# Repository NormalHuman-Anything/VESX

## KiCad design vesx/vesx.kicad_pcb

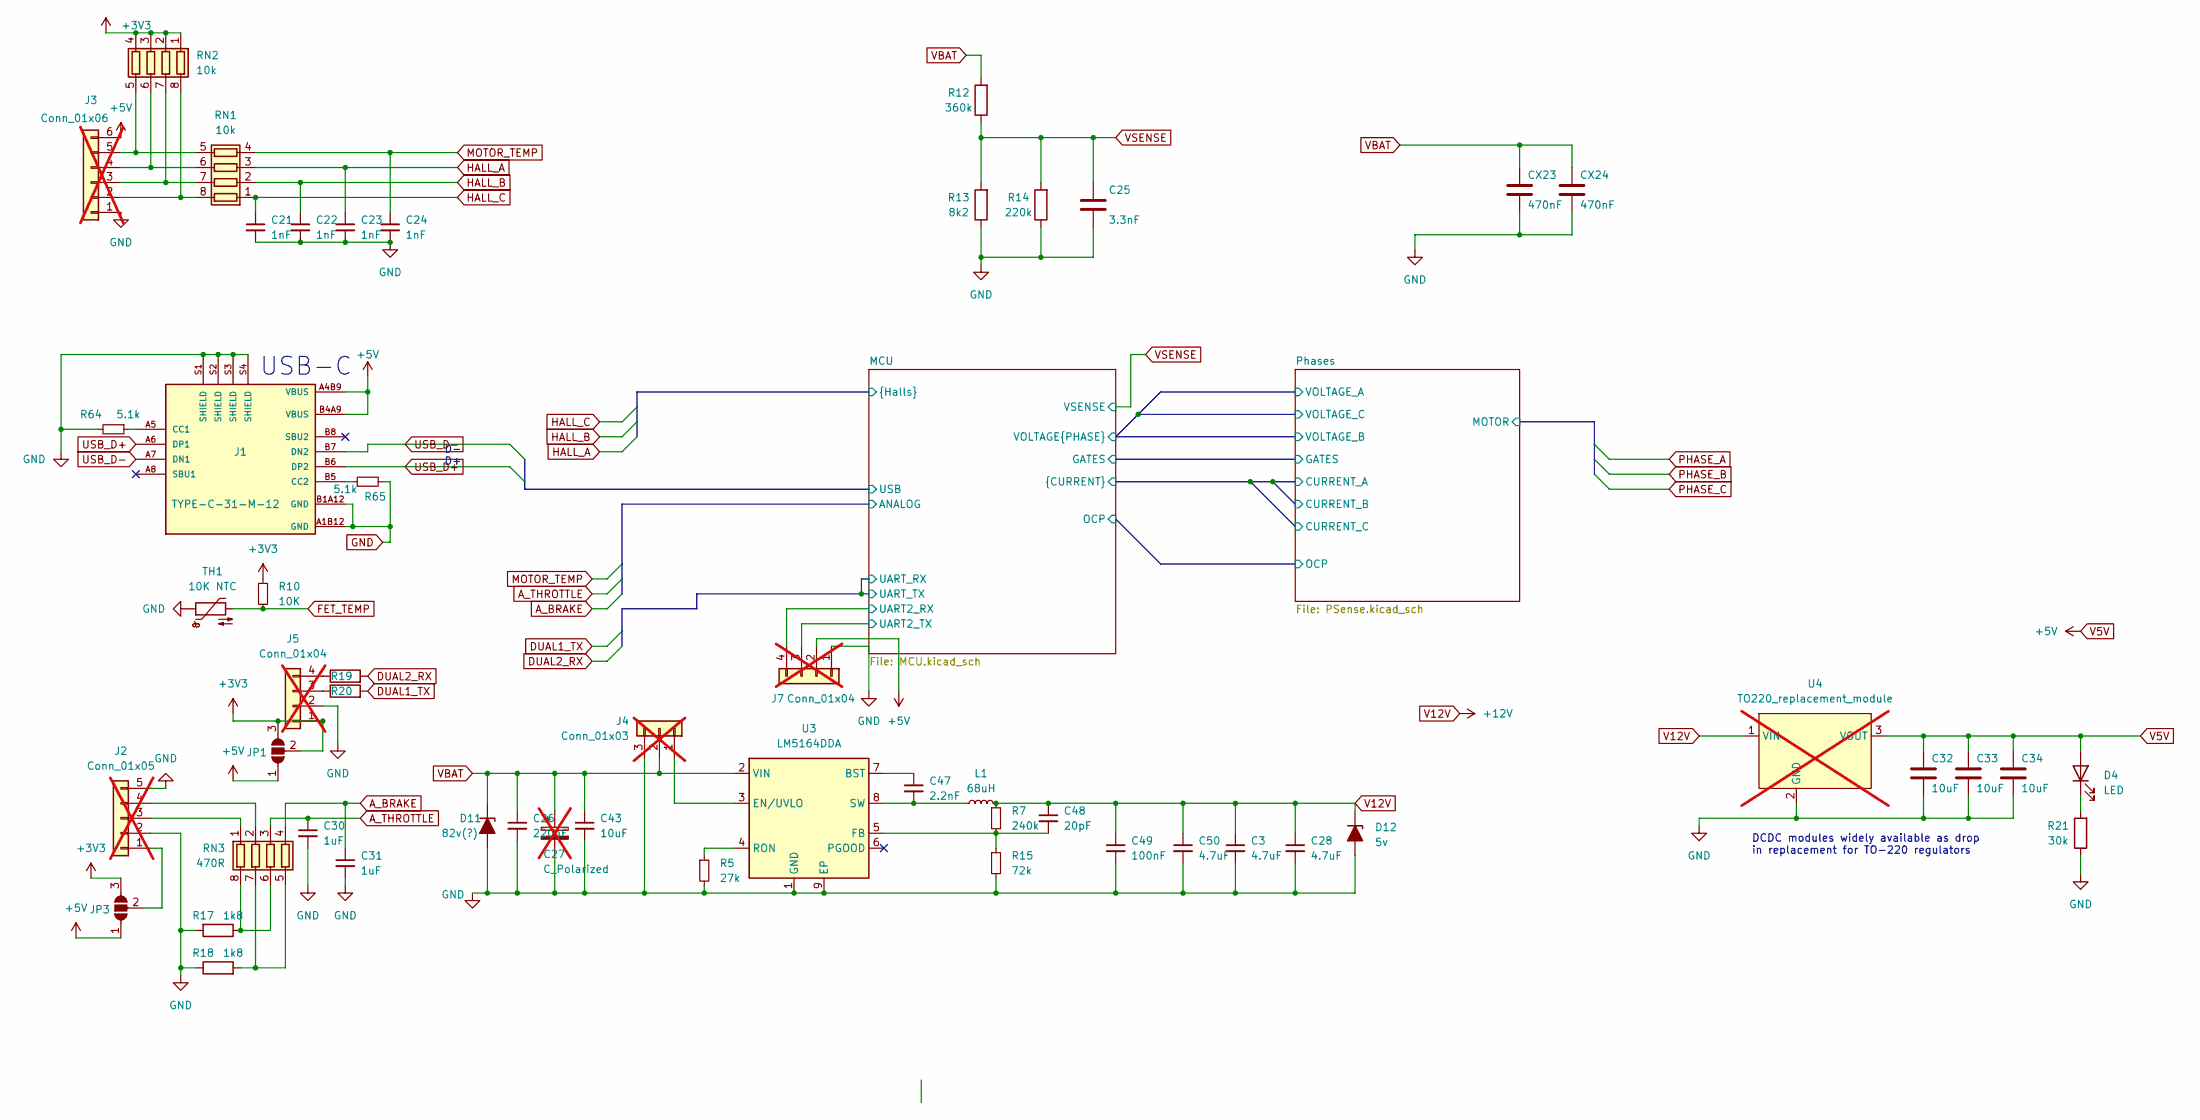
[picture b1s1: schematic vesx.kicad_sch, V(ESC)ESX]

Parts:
C3, C28, C50: 4.7uF; C_0603_1608Metric; LCSC C237615
C21, C22, C23, C24: 1nF; C_0603_1608Metric; LCSC C1588
C25: 3.3nF; C_0603_1608Metric; LCSC C1613
C26: 220nF; C_0603_1608Metric; LCSC C6119850
C27: C_Polarized; CP_Radial_D8.0mm_P3.50mm; not fitted
C30, C31: 1uF; C_0603_1608Metric; LCSC C15849
C32, C33, C34, C43: 10uF; C_0603_1608Metric; LCSC C96446
C47: 2.2nF; C_0603_1608Metric; LCSC C113804
C48: 20pF; C_0402_1005Metric; LCSC C343868
C49: 100nF; C_0603_1608Metric; LCSC C14663
CX23, CX24: 470nF; C_1210_3225Metric; LCSC C192761
D4: LED; LED_0603_1608Metric; LCSC C72041
D11: 82v(?); D_SOD-123F; LCSC C2903858
D12: 5v; D_SOD-323; LCSC C508230
J1: TYPE-C-31-M-12; USB_C_Receptacle_HRO_TYPE-C-31-M-12; PARTREV A; LCSC C165948
J2: Conn_01x05; JST_PH_B5B-PH-K_1x05_P2.00mm_Vertical; not fitted
J3: Conn_01x06; JST_PH_B6B-PH-K_1x06_P2.00mm_Vertical; not fitted
J4: Conn_01x03; JST_PH_B3B-PH-K_1x03_P2.00mm_Vertical; not fitted
J5: Conn_01x04; JST_PH_B4B-PH-K_1x04_P2.00mm_Vertical; not fitted
J7: Conn_01x04; PinHeader_1x04_P1.00mm_Vertical; not fitted
JP1, JP3: SolderJumper_3_Open; SolderJumper-3_P1.3mm_Open_RoundedPad1.0x1.5mm_NumberLabels
L1: 68uH; L_TracoPower_TCK-047_5.2x5.8mm; LCSC C5362907
R5: 27k; R_0603_1608Metric; LCSC C3016359
R7: 240k; R_0603_1608Metric; LCSC C269687
R10: 10K; R_0603_1608Metric; LCSC C25804
R12: 360k; R_0805_2012Metric; LCSC C17645
R13: 8k2; R_0603_1608Metric; LCSC C25981
R14: 220k; R_0603_1608Metric; LCSC C22961
R15: 72k; R_0603_1608Metric; LCSC C2828635
R17, R18: 1k8; R_0603_1608Metric; LCSC C4177
R19, R20: R100; R_0603_1608Metric; LCSC C22775
R21: 30k; R_0603_1608Metric; LCSC C22984
R64, R65: 5.1k; R_0402_1005Metric; LCSC C105872
RN1, RN2: 10k; R_Array_Concave_4x0603; LCSC C20624287
RN3: 470R; R_Array_Concave_4x0603; LCSC C25510
TH1: 10K NTC; R_0603_1608Metric; LCSC C167506
U3: LM5164DDA; HSOP-8-1EP_3.9x4.9mm_P1.27mm_EP2.41x3.1mm_ThermalVias; LCSC C477928
U4: TO220_replacement_module; not fitted

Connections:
+3V3: J5.1, JP1.2 (C), JP1.3 (B), JP3.3 (B), R10.1, RN2.1 (R1.1), RN2.2 (R2.1), RN2.3 (R3.1), RN2.4 (R4.1); also elsewhere on the board
/MCU/UART2_RX: J7.4; also elsewhere on the board
/MCU/UART2_TX: J7.3; also elsewhere on the board
A_BRAKE: C31.1, RN3.4 (R4.1); also elsewhere on the board
A_THROTTLE: C30.1, RN3.3 (R3.1); also elsewhere on the board
DUAL1_TX: R20.2; also elsewhere on the board
DUAL2_RX: R19.2; also elsewhere on the board
FET_TEMP: R10.2, TH1.2; also elsewhere on the board
GND: C3.2, C21.2, C22.2, C23.2, C24.2, C25.2, C26.2, C27.2, C28.2, C30.2, C31.2, C32.2, C33.2, C34.2, C43.2, C49.2, C50.2, CX23.2, CX24.2, D11.2 (A), D12.2 (A), J1.A1B12 (GND), J1.B1A12 (GND), J1.S1 (SHIELD), J1.S2 (SHIELD), J1.S3 (SHIELD), J1.S4 (SHIELD), J2.2, J2.5, J3.1, J4.3, J5.2, J7.1, R5.2, R13.1, R14.1, R15.2, R17.2, R18.1, R21.1, R64.2, R65.2, TH1.1, U3.1 (GND), U3.9 (EP), U4.2 (GND); also elsewhere on the board
HALL_A: C23.1, RN1.3 (R3.1)
HALL_B: C22.1, RN1.2 (R2.1)
HALL_C: C21.1, RN1.1 (R1.1)
MOTOR_TEMP: C24.1, RN1.4 (R4.1); also elsewhere on the board
unnamed: D4.1 (K), R21.2
unnamed: J1.A5 (CC1), R64.1
unnamed: J1.B5 (CC2), R65.1
unnamed: J2.1, JP3.2 (C)
unnamed: J2.3, RN3.1 (R1.1)
unnamed: J2.4, RN3.2 (R2.1)
unnamed: J3.2, RN1.8 (R1.2), RN2.8 (R1.2)
unnamed: J3.3, RN1.7 (R2.2), RN2.7 (R2.2)
unnamed: J3.4, RN1.6 (R3.2), RN2.6 (R3.2)
unnamed: J3.5, RN1.5 (R4.2), RN2.5 (R4.2)
unnamed: J4.1, U3.3 (EN/UVLO)
unnamed: J5.3, R20.1
unnamed: J5.4, R19.1
unnamed: R17.1, RN3.6 (R3.2), RN3.8 (R1.2)
unnamed: R18.2, RN3.5 (R4.2), RN3.7 (R2.2)
unnamed: C47.1, U3.7 (BST)
unnamed: C48.2, R7.2, R15.1, U3.5 (FB)
unnamed: R5.1, U3.4 (RON)
unnamed: C47.2, L1.1, U3.8 (SW)
USB_D+: J1.A6 (DP1), J1.B6 (DP2); also elsewhere on the board
USB_D-: J1.A7 (DN1), J1.B7 (DN2); also elsewhere on the board
V5V: C32.1, C33.1, C34.1, D4.2 (A), J1.A4B9 (VBUS), J1.B4A9 (VBUS), J3.6, J7.2, JP1.1 (A), JP3.1 (A), U4.3 (VOUT); also elsewhere on the board
V12V: C3.1, C28.1, C48.1, C49.1, C50.1, D12.1 (K), L1.2, R7.1, U4.1 (VIN); also elsewhere on the board
VBAT: C26.1, C27.1, C43.1, CX23.1, CX24.1, D11.1 (K), J4.2, R12.2, U3.2 (VIN); also elsewhere on the board
VSENSE: C25.1, R12.1, R13.2, R14.2; also elsewhere on the board

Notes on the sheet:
DCDC modules widely available as drop in replacement for TO-220 regulators
D- D+
USB-C

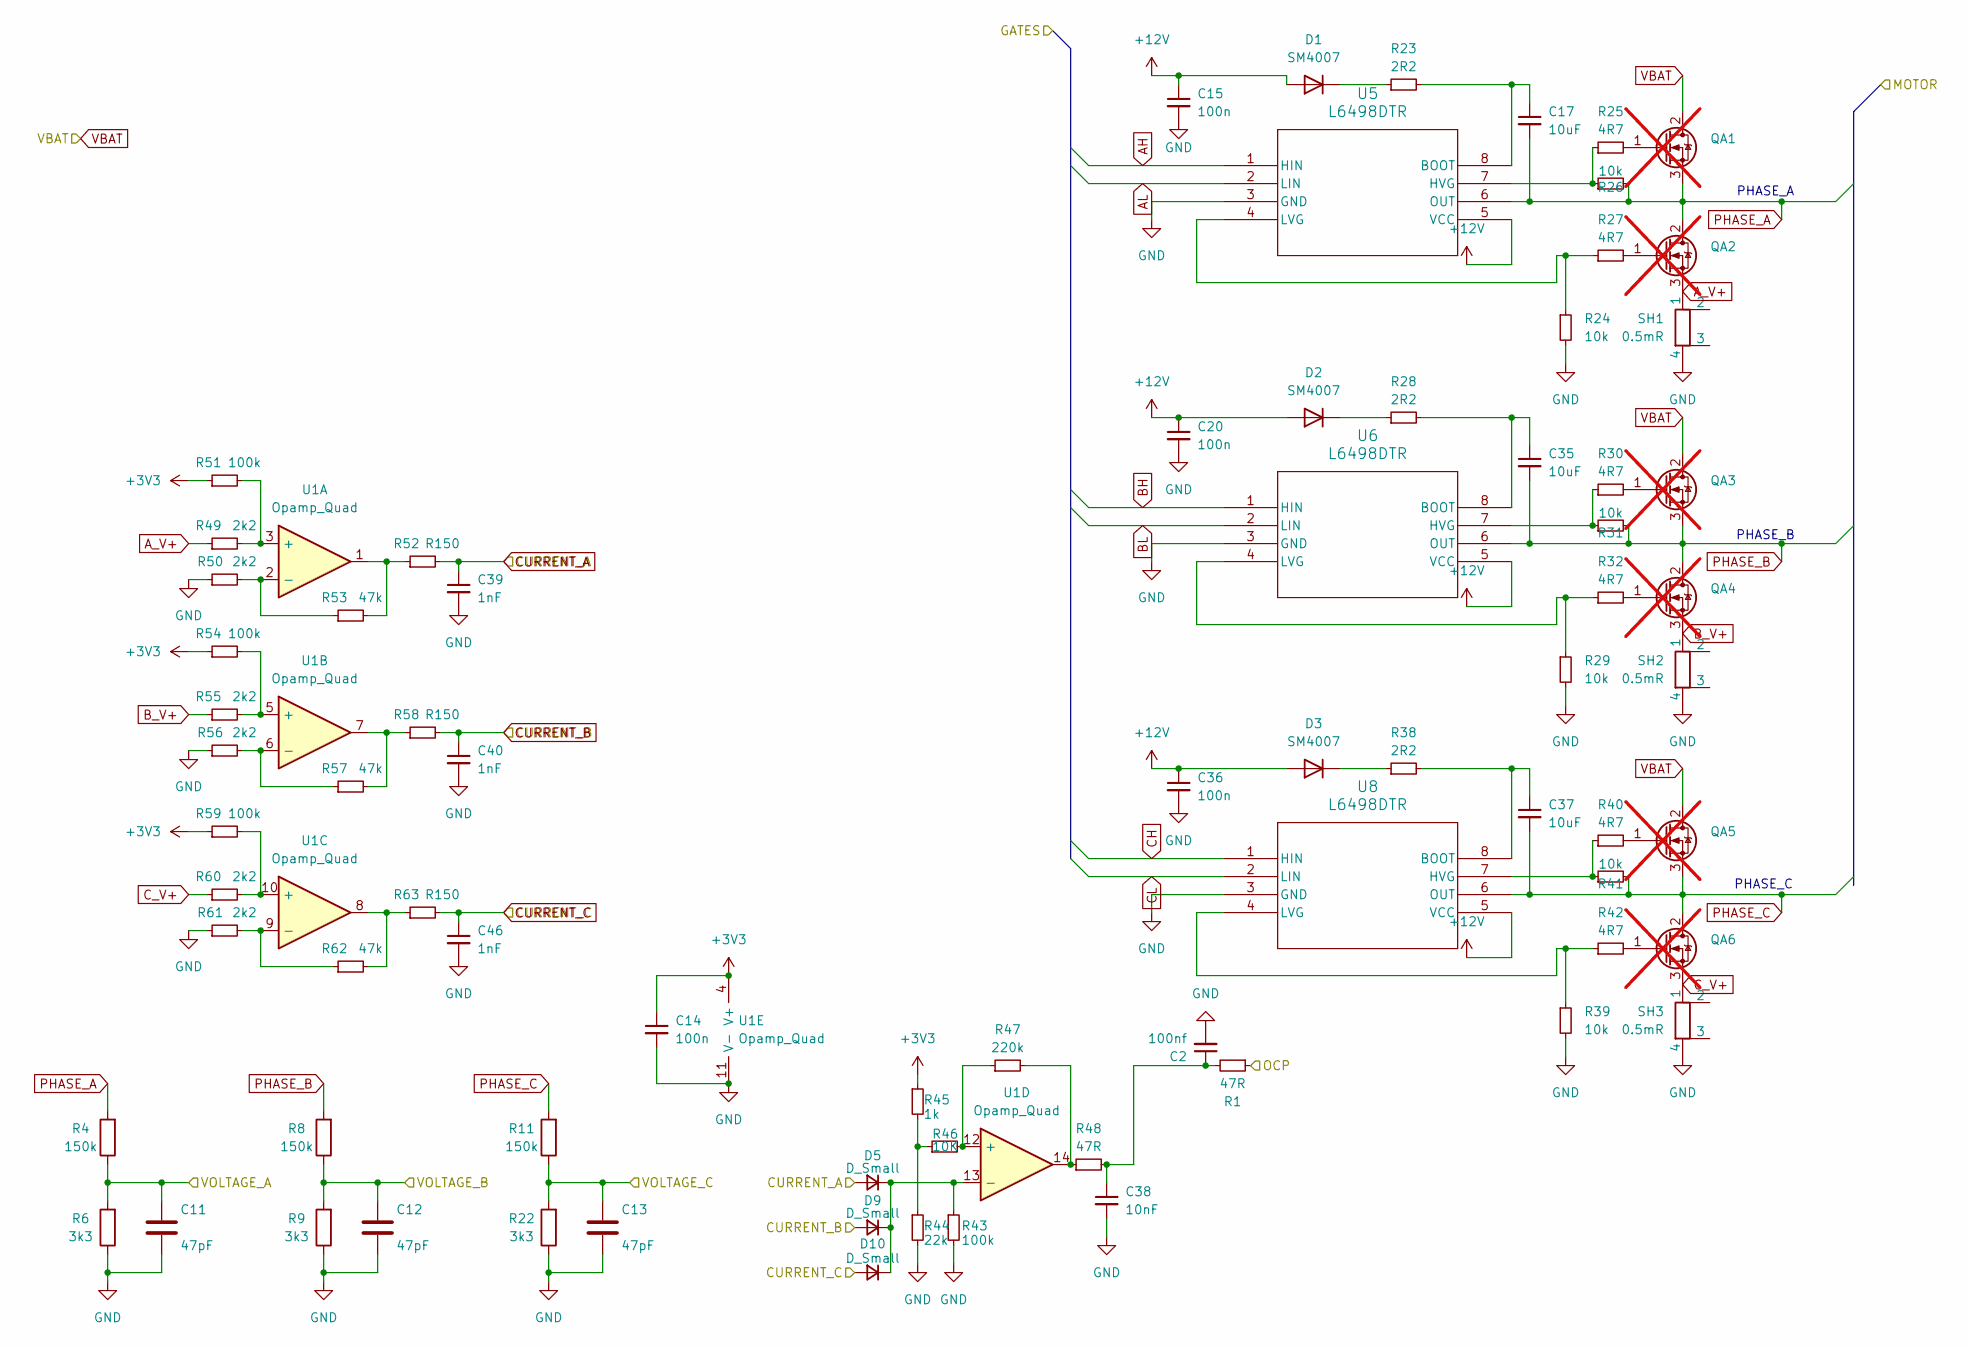
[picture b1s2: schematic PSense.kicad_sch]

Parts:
C2: 100nf; C_0402_1005Metric; LCSC C1525
C11, C12, C13: 47pF; C_0603_1608Metric; LCSC C1671
C14, C15, C20, C36: 100n; C_0603_1608Metric; LCSC C14663
C17, C35, C37: 10uF; C_0603_1608Metric; LCSC C96446
C38: 10nF; C_0603_1608Metric; LCSC C57112
C39, C40, C46: 1nF; C_0603_1608Metric; LCSC C1588
D1, D2, D3: SM4007; D_MELF; LCSC C412437
D5, D9, D10: D_Small; D_SOD-323; LCSC C191023
QA1, QA2, QA3, QA4, QA5, QA6: CRST030N10N; TO-220-3_Vertical; not fitted
R1: 47R; R_0402_1005Metric; LCSC C25118
R4, R8, R11: 150k; R_0805_2012Metric; LCSC C17470
R6, R9, R22: 3k3; R_0603_1608Metric; LCSC C22978
R23, R28, R38: 2R2; R_0603_1608Metric; LCSC C22939
R24, R26, R29, R31, R39, R41: 10k; R_0603_1608Metric; LCSC C25804
R25, R27, R30, R32, R40, R42: 4R7; R_0603_1608Metric; LCSC C23214
R43, R51, R54, R59: 100k; R_0603_1608Metric; LCSC C25803
R44: 22k; R_0603_1608Metric; LCSC C31850
R45: 1k; R_0603_1608Metric; LCSC C21190
R46: 10K; R_0603_1608Metric; LCSC C25804
R47: 220k; R_0603_1608Metric; LCSC C22961
R48: 47R; R_0603_1608Metric; LCSC C23182
R49, R50, R55, R56, R60, R61: 2k2; R_0603_1608Metric; LCSC C4190
R52, R58, R63: R150; R_0603_1608Metric; LCSC C22808
R53, R57, R62: 47k; R_0603_1608Metric; LCSC C25819
SH1, SH2, SH3: 0.5mR; Shunt_2512_6332Metric; LCSC C7178835
U1: Opamp_Quad; SOIC-14_3.9x8.7mm_P1.27mm; LCSC C695777
U5, U6, U8: L6498DTR; SO-8_STM; LCSC C500658

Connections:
+3V3: C14.1, R45.1, R51.1, R54.1, R59.1, U1.4 (V+); also elsewhere on the board
/MCU/OCP: R1.1; also elsewhere on the board
AH: U5.1 (HIN); also elsewhere on the board
AL: U5.2 (LIN); also elsewhere on the board
A_V+: QA2.3, R49.1, SH1.1
BH: U6.1 (HIN); also elsewhere on the board
BL: U6.2 (LIN); also elsewhere on the board
B_V+: QA4.3, R55.1, SH2.1
CH: U8.1 (HIN); also elsewhere on the board
CL: U8.2 (LIN); also elsewhere on the board
CURRENT_A: C39.1, D5.2 (A), R52.2; also elsewhere on the board
CURRENT_B: C40.1, D9.2 (A), R58.2; also elsewhere on the board
CURRENT_C: C46.1, D10.2 (A), R63.2; also elsewhere on the board
C_V+: QA6.3, R60.1, SH3.1
GND: C2.2, C11.2, C12.2, C13.2, C14.2, C15.2, C20.2, C36.2, C38.2, C39.2, C40.2, C46.2, R6.1, R9.1, R22.1, R24.2, R29.2, R39.2, R43.2, R44.2, R50.1, R56.1, R61.1, SH1.4, SH2.4, SH3.4, U1.11 (V-), U5.3 (GND), U6.3 (GND), U8.3 (GND); also elsewhere on the board
unnamed: C2.1, C38.1, R1.2, R48.2
unnamed: D1.1 (K), R23.1
unnamed: D2.1 (K), R28.1
unnamed: D3.1 (K), R38.1
unnamed: D5.1 (K), D9.1 (K), D10.1 (K), R43.1, U1.13 (-)
unnamed: QA1.1, R25.2
unnamed: QA2.1, R27.2
unnamed: QA3.1, R30.2
unnamed: QA4.1, R32.2
unnamed: QA5.1, R40.2
unnamed: QA6.1, R42.2
unnamed: R44.1, R45.2, R46.1
unnamed: R47.2, R48.1, U1.14
unnamed: R52.1, R53.2, U1.1
unnamed: R57.2, R58.1, U1.7
unnamed: R62.2, R63.1, U1.8
unnamed: R49.2, R51.2, U1.3 (+)
unnamed: R50.2, R53.1, U1.2 (-)
unnamed: R54.2, R55.2, U1.5 (+)
unnamed: R56.2, R57.1, U1.6 (-)
unnamed: R59.2, R60.2, U1.10 (+)
unnamed: R61.2, R62.1, U1.9 (-)
unnamed: R46.2, R47.1, U1.12 (+)
unnamed: C17.1, R23.2, U5.8 (BOOT)
unnamed: R25.1, R26.1, U5.7 (HVG)
unnamed: R24.1, R27.1, U5.4 (LVG)
unnamed: C35.1, R28.2, U6.8 (BOOT)
unnamed: R30.1, R31.1, U6.7 (HVG)
unnamed: R29.1, R32.1, U6.4 (LVG)
unnamed: C37.1, R38.2, U8.8 (BOOT)
unnamed: R40.1, R41.1, U8.7 (HVG)
unnamed: R39.1, R42.1, U8.4 (LVG)
PA0: C11.1, R4.1, R6.2; also elsewhere on the board
PA1: C12.1, R8.1, R9.2; also elsewhere on the board
PA2: C13.1, R11.1, R22.2; also elsewhere on the board
PHASE_A: C17.2, QA1.3, QA2.2, R4.2, R26.2, U5.6 (OUT); also elsewhere on the board
PHASE_B: C35.2, QA3.3, QA4.2, R8.2, R31.2, U6.6 (OUT); also elsewhere on the board
PHASE_C: C37.2, QA5.3, QA6.2, R11.2, R41.2, U8.6 (OUT); also elsewhere on the board
V12V: C15.1, C20.1, C36.1, D1.2 (A), D2.2 (A), D3.2 (A), U5.5 (VCC), U6.5 (VCC), U8.5 (VCC); also elsewhere on the board
VBAT: QA1.2, QA3.2, QA5.2; also elsewhere on the board

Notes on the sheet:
PHASE_B
PHASE_C
PHASE_A

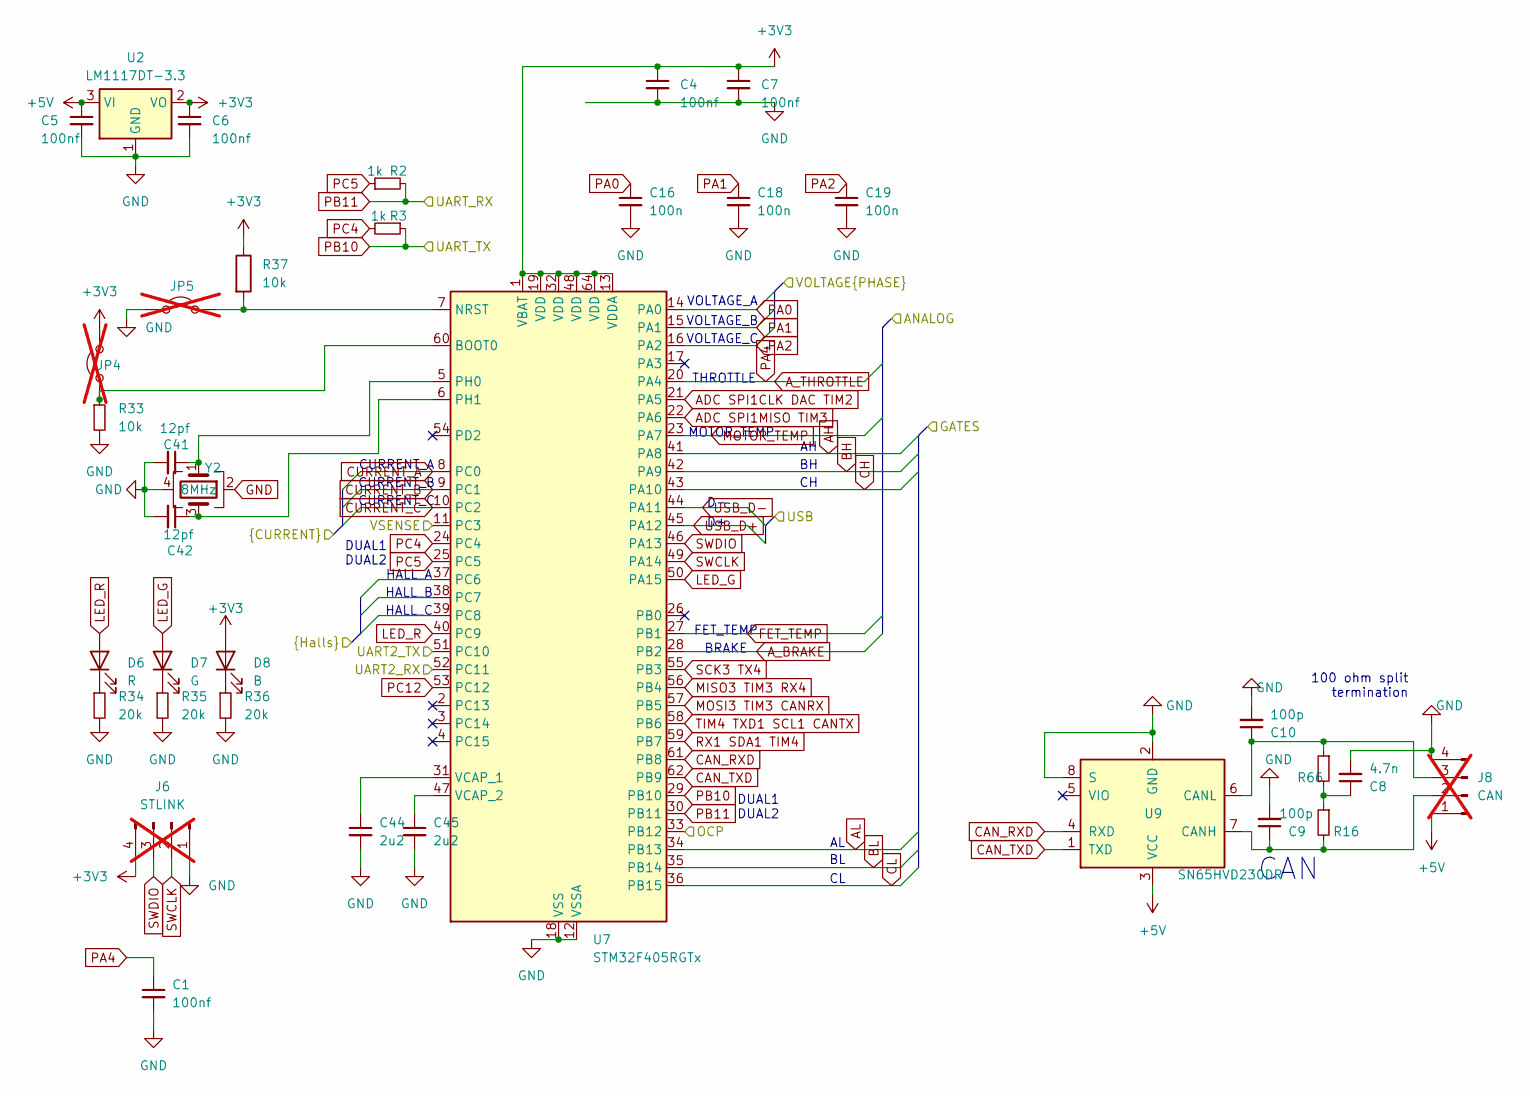
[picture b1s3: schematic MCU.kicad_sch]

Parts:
C1: 100nf; C_0402_1005Metric; LCSC C1525
C4, C6, C7: 100nf; C_0603_1608Metric; LCSC C1952781
C5: 100nf; CP_EIA-3216-18_Kemet-A; LCSC C122257
C8: 4.7n; C_0402_1005Metric; LCSC C1538
C9, C10: 100p; C_0402_1005Metric; LCSC C1546
C16, C18, C19: 100n; C_0402_1005Metric; LCSC C1525
C41, C42: 12pf; C_0603_1608Metric; LCSC C519482
C44, C45: 2u2; C_0603_1608Metric; LCSC C23630
D6: R; LED_0603_1608Metric; LCSC C2286
D7: G; LED_0603_1608Metric; LCSC C87326
D8: B; LED_0603_1608Metric; LCSC C2689219
J6: STLINK; PinHeader_2x02_P2.00mm_Vertical; not fitted
J8: CAN; JST_PH_B4B-PH-K_1x04_P2.00mm_Vertical; not fitted
JP4, JP5: Jumper_2_Open; PinHeader_1x02_P2.54mm_Vertical; not fitted
R2, R3: 1k; R_0402_1005Metric; LCSC C11702
R16, R66: 100Ω; R_0402_1005Metric; LCSC C25076
R33: 10k; R_0603_1608Metric; LCSC C25804
R34, R35, R36: 20k; R_0603_1608Metric; LCSC C269687
R37: 10k; R_0402_1005Metric; LCSC C25804
U2: LM1117DT-3.3; SOT-223-3_TabPin2; LCSC C126027
U7: STM32F405RGTx; LQFP-64_10x10mm_P0.5mm; LCSC C15742
U9: SN65HVD230DR; SOIC-8_3.9x4.9mm_P1.27mm; LCSC C12084
Y2: 8MHz; Crystal_SMD_3225-4Pin_3.2x2.5mm; LCSC C518154

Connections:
+3V3: C4.1, C6.1, C7.1, D8.2 (A), J6.4, JP4.2 (B), R37.1, U2.2 (VO), U7.1 (VBAT), U7.13 (VDDA), U7.19 (VDD), U7.32 (VDD), U7.48 (VDD), U7.64 (VDD); also elsewhere on the board
/MCU/OCP: U7.33 (PB12); also elsewhere on the board
/MCU/UART2_RX: U7.52 (PC11); also elsewhere on the board
/MCU/UART2_TX: U7.51 (PC10); also elsewhere on the board
ADC SPI1CLK DAC TIM2: U7.21 (PA5)
ADC SPI1MISO TIM3: U7.22 (PA6)
AH: U7.41 (PA8); also elsewhere on the board
AL: U7.34 (PB13); also elsewhere on the board
A_BRAKE: U7.28 (PB2); also elsewhere on the board
A_THROTTLE: C1.1, U7.20 (PA4); also elsewhere on the board
BH: U7.42 (PA9); also elsewhere on the board
BL: U7.35 (PB14); also elsewhere on the board
CAN_RXD: U7.61 (PB8), U9.4 (RXD)
CAN_TXD: U7.62 (PB9), U9.1 (TXD)
CH: U7.43 (PA10); also elsewhere on the board
CL: U7.36 (PB15); also elsewhere on the board
CURRENT_A: U7.8 (PC0); also elsewhere on the board
CURRENT_B: U7.9 (PC1); also elsewhere on the board
CURRENT_C: U7.10 (PC2); also elsewhere on the board
DUAL1_TX: R3.1, U7.29 (PB10); also elsewhere on the board
DUAL2_RX: R2.2, U7.30 (PB11); also elsewhere on the board
FET_TEMP: U7.27 (PB1); also elsewhere on the board
GND: C1.2, C4.2, C5.2, C6.2, C7.2, C8.2, C9.2, C10.2, C16.2, C18.2, C19.2, C41.2, C42.2, C44.2, C45.2, J6.1, J8.4, JP5.1 (A), R33.2, R34.2, R35.2, R36.2, U2.1 (GND), U7.12 (VSSA), U7.18 (VSS), U7.63 (VSS), U9.2 (GND), U9.8 (S), Y2.2, Y2.4; also elsewhere on the board
LED_G: D7.2 (A), U7.50 (PA15)
LED_R: D6.2 (A), U7.40 (PC9)
MISO3 TIM3 RX4: U7.56 (PB4)
MOSI3 TIM3 CANRX: U7.57 (PB5)
MOTOR_TEMP: U7.23 (PA7); also elsewhere on the board
unnamed: C8.1, R16.1, R66.2
unnamed: D6.1 (K), R34.1
unnamed: D7.1 (K), R35.1
unnamed: D8.1 (K), R36.1
unnamed: C9.1, J8.2, R16.2, U9.7 (CANH)
unnamed: C10.1, J8.3, R66.1, U9.6 (CANL)
unnamed: JP4.1 (A), R33.1, U7.60 (BOOT0)
unnamed: JP5.2 (B), R37.2, U7.7 (NRST)
unnamed: C41.1, U7.5 (PH0), Y2.1
unnamed: C42.1, U7.6 (PH1), Y2.3
unnamed: C44.1, U7.31 (VCAP_1)
unnamed: C45.1, U7.47 (VCAP_2)
PA0: C16.1, U7.14 (PA0); also elsewhere on the board
PA1: C18.1, U7.15 (PA1); also elsewhere on the board
PA2: C19.1, U7.16 (PA2); also elsewhere on the board
PC4: R3.2, U7.24 (PC4)
PC5: R2.1, U7.25 (PC5)
PC12: U7.53 (PC12)
RX1 SDA1 TIM4: U7.59 (PB7)
SCK3 TX4: U7.55 (PB3)
SWCLK: J6.2, U7.49 (PA14)
SWDIO: J6.3, U7.46 (PA13)
TIM4 TXD1 SCL1 CANTX: U7.58 (PB6)
USB_D+: U7.45 (PA12); also elsewhere on the board
USB_D-: U7.44 (PA11); also elsewhere on the board
V5V: C5.1, J8.1, U2.3 (VI), U9.3 (VCC); also elsewhere on the board
VSENSE: U7.11 (PC3); also elsewhere on the board

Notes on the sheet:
HALL_C
CURRENT_A
HALL_B
100 ohm split termination
VOLTAGE_C
DUAL1 DUAL2
VOLTAGE_A
HALL_A
THROTTLE
CURRENT_B
FET_TEMP
VOLTAGE_B
BRAKE
CURRENT_C
MOTOR_TEMP
CAN

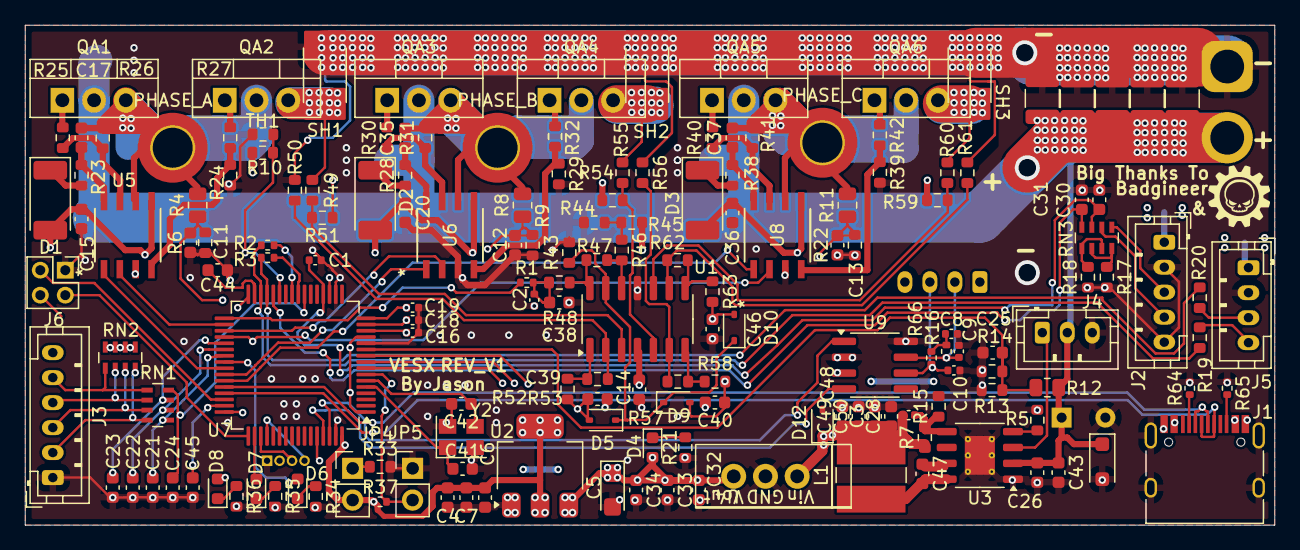
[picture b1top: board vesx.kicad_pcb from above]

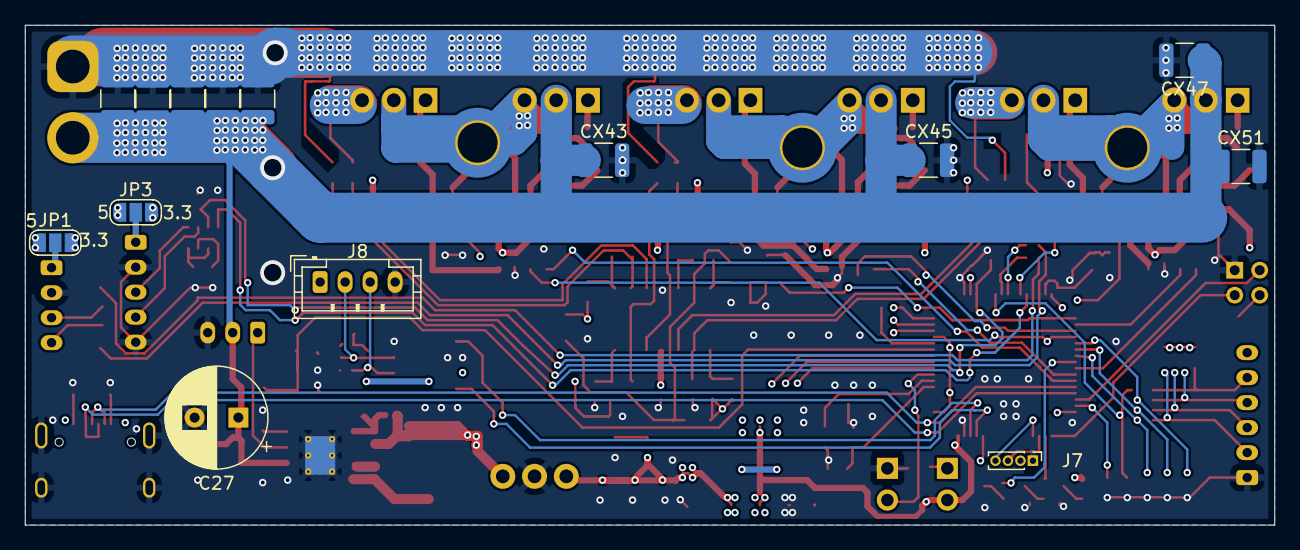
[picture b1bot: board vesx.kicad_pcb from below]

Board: 4 copper layers, 100.0 x 40.0 mm, 180 parts (14 on the bottom side), 109 nets.

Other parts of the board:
CX10, CX11, CX12, CX13, CX25, CX26, CX28, CX30, CX43, CX45, CX47, CX51: 470nF; C_1210_3225Metric
PHASE_A: MountingHole_3.0mm_Pad; MountingHole_3.2mm_M3_DIN965_Pad_TopBottom
PHASE_B: MountingHole_3.5mm_Pad; MountingHole_3.2mm_M3_DIN965_Pad_TopBottom
PHASE_C: MountingHole_3.2mm_M3_DIN965_Pad_TopBottom

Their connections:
GND: CX10.2, CX11.2, CX12.2, CX13.2, CX25.2, CX26.2, CX28.2, CX30.2, CX43.2, CX45.2, CX47.2, CX51.2; also elsewhere on the board
PHASE_A: PHASE_A.1; also elsewhere on the board
PHASE_B: PHASE_B.1; also elsewhere on the board
PHASE_C: PHASE_C.1; also elsewhere on the board
VBAT: CX10.1, CX11.1, CX12.1, CX13.1, CX25.1, CX26.1, CX28.1, CX30.1, CX43.1, CX45.1, CX47.1, CX51.1; also elsewhere on the board

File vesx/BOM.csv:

"Reference","Value","Footprint","Qty","LCSC"
"C9,C10","100p","Capacitor_SMD:C_0402_1005Metric","2","C1546"
"QA1,QA2,QA3,QA4,QA5,QA6","CRST030N10N","Package_TO_SOT_THT:TO-220-3_Vertical","6",""
"R16,R66","100Ω","Resistor_SMD:R_0402_1005Metric","2","C25076"
"R64,R65","5.1k","Resistor_SMD:R_0402_1005Metric","2","C105872"
"U4","TO220_replacement_module","CCC_ESC_Custom_parts:TO220_replacement_module","1",""
"D1,D2,D3","SM4007","Diode_SMD:D_MELF","3"," C412437"
"U2","LM1117DT-3.3","Package_TO_SOT_SMD:SOT-223-3_TabPin2","1","C126027"
"U9","SN65HVD230DR","Package_SO:SOIC-8_3.9x4.9mm_P1.27mm","1","C12084"
"C8","4.7n","Capacitor_SMD:C_0402_1005Metric","1","C1538"
"J1","TYPE-C-31-M-12","Connector_USB:USB_C_Receptacle_HRO_TYPE-C-31-M-12","1","C165948"
"U7","STM32F405RGTx","Package_QFP:LQFP-64_10x10mm_P0.5mm","1","C15742"
"U3","LM5164DDA","Package_SO:HSOP-8-1EP_3.9x4.9mm_P1.27mm_EP2.41x3.1mm_ThermalVias","1","C477928"
"U5,U6,U8","L6498DTR","vvvv:SO-8_STM","3","C500658"
"C1","100nf","Capacitor_SMD:C_0402_1005Metric","1","C1525 "
"C2","100nf","Capacitor_SMD:C_0402_1005Metric","1","C1525"
"C3,C28,C50","4.7uF","Capacitor_SMD:C_0603_1608Metric","3","C237615"
"C4,C6,C7","100nf","Capacitor_SMD:C_0603_1608Metric","3","C1952781"
"C5","100nf","Capacitor_Tantalum_SMD:CP_EIA-3216-18_Kemet-A","1","C122257"
"C11,C12,C13","47pF","Capacitor_SMD:C_0603_1608Metric","3"," C1671"
"C14,C15","100n","Capacitor_SMD:C_0603_1608Metric","2","C14663"
"C16,C18,C19","100n","Capacitor_SMD:C_0402_1005Metric","3","C1525 "
"C17,C35,C37,C43","10uF","Capacitor_SMD:C_0603_1608Metric","4"," C96446"
"C20,C36","100n","Capacitor_SMD:C_0603_1608Metric","2"," C14663"
"C21,C22,C23,C24,C39,C40,C46","1nF","Capacitor_SMD:C_0603_1608Metric","7"," C1588"
"C25","3.3nF","Capacitor_SMD:C_0603_1608Metric","1","C1613"
"C26","220nF","Capacitor_SMD:C_0603_1608Metric","1","C6119850"
"C27","C_Polarized","Capacitor_THT:CP_Radial_D8.0mm_P3.50mm","1",""
"C30,C31","1uF","Capacitor_SMD:C_0603_1608Metric","2","C15849"
"C32,C33,C34","10uF","Capacitor_SMD:C_0603_1608Metric","3","C96446"
"C38","10nF","Capacitor_SMD:C_0603_1608Metric","1"," C57112"
"C41,C42","12pf","Capacitor_SMD:C_0603_1608Metric","2","C519482"
"C44,C45","2u2","Capacitor_SMD:C_0603_1608Metric","2","C23630"
"C47","2.2nF","Capacitor_SMD:C_0603_1608Metric","1","C113804"
"C48","20pF","Capacitor_SMD:C_0402_1005Metric","1","C343868"
"C49","100nF","Capacitor_SMD:C_0603_1608Metric","1","C14663"
"CX23,CX24","470nF","Capacitor_SMD:C_1210_3225Metric","2","C192761"
"D4","LED","LED_SMD:LED_0603_1608Metric","1","C72041"
"D5,D9,D10","D_Small","Diode_SMD:D_SOD-323","3","C191023"
"D6","R","LED_SMD:LED_0603_1608Metric","1","C2286"
"D7","G","LED_SMD:LED_0603_1608Metric","1","C87326"
"D8","B","LED_SMD:LED_0603_1608Metric","1","C2689219"
"D11","82v(?)","Diode_SMD:D_SOD-123F","1","C2903858"
"D12","5v","Diode_SMD:D_SOD-323","1","C508230"
"J2","Conn_01x05","Connector_JST:JST_PH_B5B-PH-K_1x05_P2.00mm_Vertical","1",""
"J3","Conn_01x06","Connector_JST:JST_PH_B6B-PH-K_1x06_P2.00mm_Vertical","1",""
"J4","Conn_01x03","Connector_JST:JST_PH_B3B-PH-K_1x03_P2.00mm_Vertical","1",""
"J5,J7","Conn_01x04","-- mixed values --","2",""
"J6","STLINK","Connector_PinHeader_2.00mm:PinHeader_2x02_P2.00mm_Vertical","1",""
"J8","CAN","Connector_JST:JST_PH_B4B-PH-K_1x04_P2.00mm_Vertical","1",""
"JP1,JP3","SolderJumper_3_Open","Jumper:SolderJumper-3_P1.3mm_Open_RoundedPad1.0x1.5mm_NumberLabels","2",""
"JP4,JP5","Jumper_2_Open","Connector_PinHeader_2.54mm:PinHeader_1x02_P2.54mm_Vertical","2",""
"L1","68uH","Inductor_SMD:L_TracoPower_TCK-047_5.2x5.8mm","1","C5362907"
"R1","47R","Resistor_SMD:R_0402_1005Metric","1","C25118"
"R2","1k","Resistor_SMD:R_0402_1005Metric","1","C11702"
"R3","1k","Resistor_SMD:R_0402_1005Metric","1","C11702 "
"R4,R8,R11","150k","Resistor_SMD:R_0805_2012Metric","3","C17470"
"R5","27k","Resistor_SMD:R_0603_1608Metric","1","C3016359"
"R6,R9,R22","3k3","Resistor_SMD:R_0603_1608Metric","3","C22978"
"R7","240k","Resistor_SMD:R_0603_1608Metric","1","C269687"
"R10,R46","10K","Resistor_SMD:R_0603_1608Metric","2","C25804"
"R12","360k","Resistor_SMD:R_0805_2012Metric","1","C17645"
"R13","8k2","Resistor_SMD:R_0603_1608Metric","1","C25981"
"R14,R47","220k","Resistor_SMD:R_0603_1608Metric","2","C22961"
"R15","72k","Resistor_SMD:R_0603_1608Metric","1","C2828635"
"R17,R18","1k8","Resistor_SMD:R_0603_1608Metric","2","C4177"
"R19,R20","R100","Resistor_SMD:R_0603_1608Metric","2","C22775"
"R21","30k","Resistor_SMD:R_0603_1608Metric","1","C22984"
"R23,R28,R38","2R2","Resistor_SMD:R_0603_1608Metric","3"," C22939"
"R24,R26,R29,R31,R33,R37,R39,R41","10k","-- mixed values --","8"," C25804"
"R25,R27,R30,R32,R40,R42","4R7","Resistor_SMD:R_0603_1608Metric","6","C23214"
"R34,R35,R36","20k","Resistor_SMD:R_0603_1608Metric","3","C269687"
"R43,R51,R54,R59","100k","Resistor_SMD:R_0603_1608Metric","4","C25803"
"R44","22k","Resistor_SMD:R_0603_1608Metric","1","C31850"
"R45","1k","Resistor_SMD:R_0603_1608Metric","1","C21190"
"R48","47R","Resistor_SMD:R_0603_1608Metric","1","C23182"
"R49,R50,R55,R56,R60,R61","2k2","Resistor_SMD:R_0603_1608Metric","6","C4190"
"R52,R58,R63","R150","Resistor_SMD:R_0603_1608Metric","3","C22808"
"R53,R57,R62","47k","Resistor_SMD:R_0603_1608Metric","3","C25819"
"RN1,RN2","10k","Resistor_SMD:R_Array_Concave_4x0603","2","C20624287"
"RN3","470R","Resistor_SMD:R_Array_Concave_4x0603","1","C25510"
"SH1,SH2,SH3","0.5mR","cccesdc:Shunt_2512_6332Metric","3","C7178835 "
"TH1","10K NTC","Resistor_SMD:R_0603_1608Metric","1","C167506"
"U1","Opamp_Quad","Package_SO:SOIC-14_3.9x8.7mm_P1.27mm","1","C695777"
"Y2","8MHz","Crystal:Crystal_SMD_3225-4Pin_3.2x2.5mm","1","C518154"

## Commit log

2024-07-28 upload
2024-07-29 vesc logo del
2024-07-29 asdf
2024-07-30 aaaaaaaaaaaaaaaaaaaaaaaaaaaaaaaaaaaaaaaa
2024-08-07 fix trace$ground plane
2024-08-07 eeeeeeeeeeeeeeeeeeee
2024-08-07 copper
2024-08-18 Revert "fix"
    This reverts commit 630a2a7c171c78306201b3488f63a123b135c984.
2024-08-18 Revert "Create .gitignore"
    This reverts commit e097b4fd8baaebda2e1c7004d7116233b601bcdd.
2024-08-18 fixed
2024-08-18 0
    0
2024-08-19 Production
2024-08-19 mistake
2024-11-07 prob final
